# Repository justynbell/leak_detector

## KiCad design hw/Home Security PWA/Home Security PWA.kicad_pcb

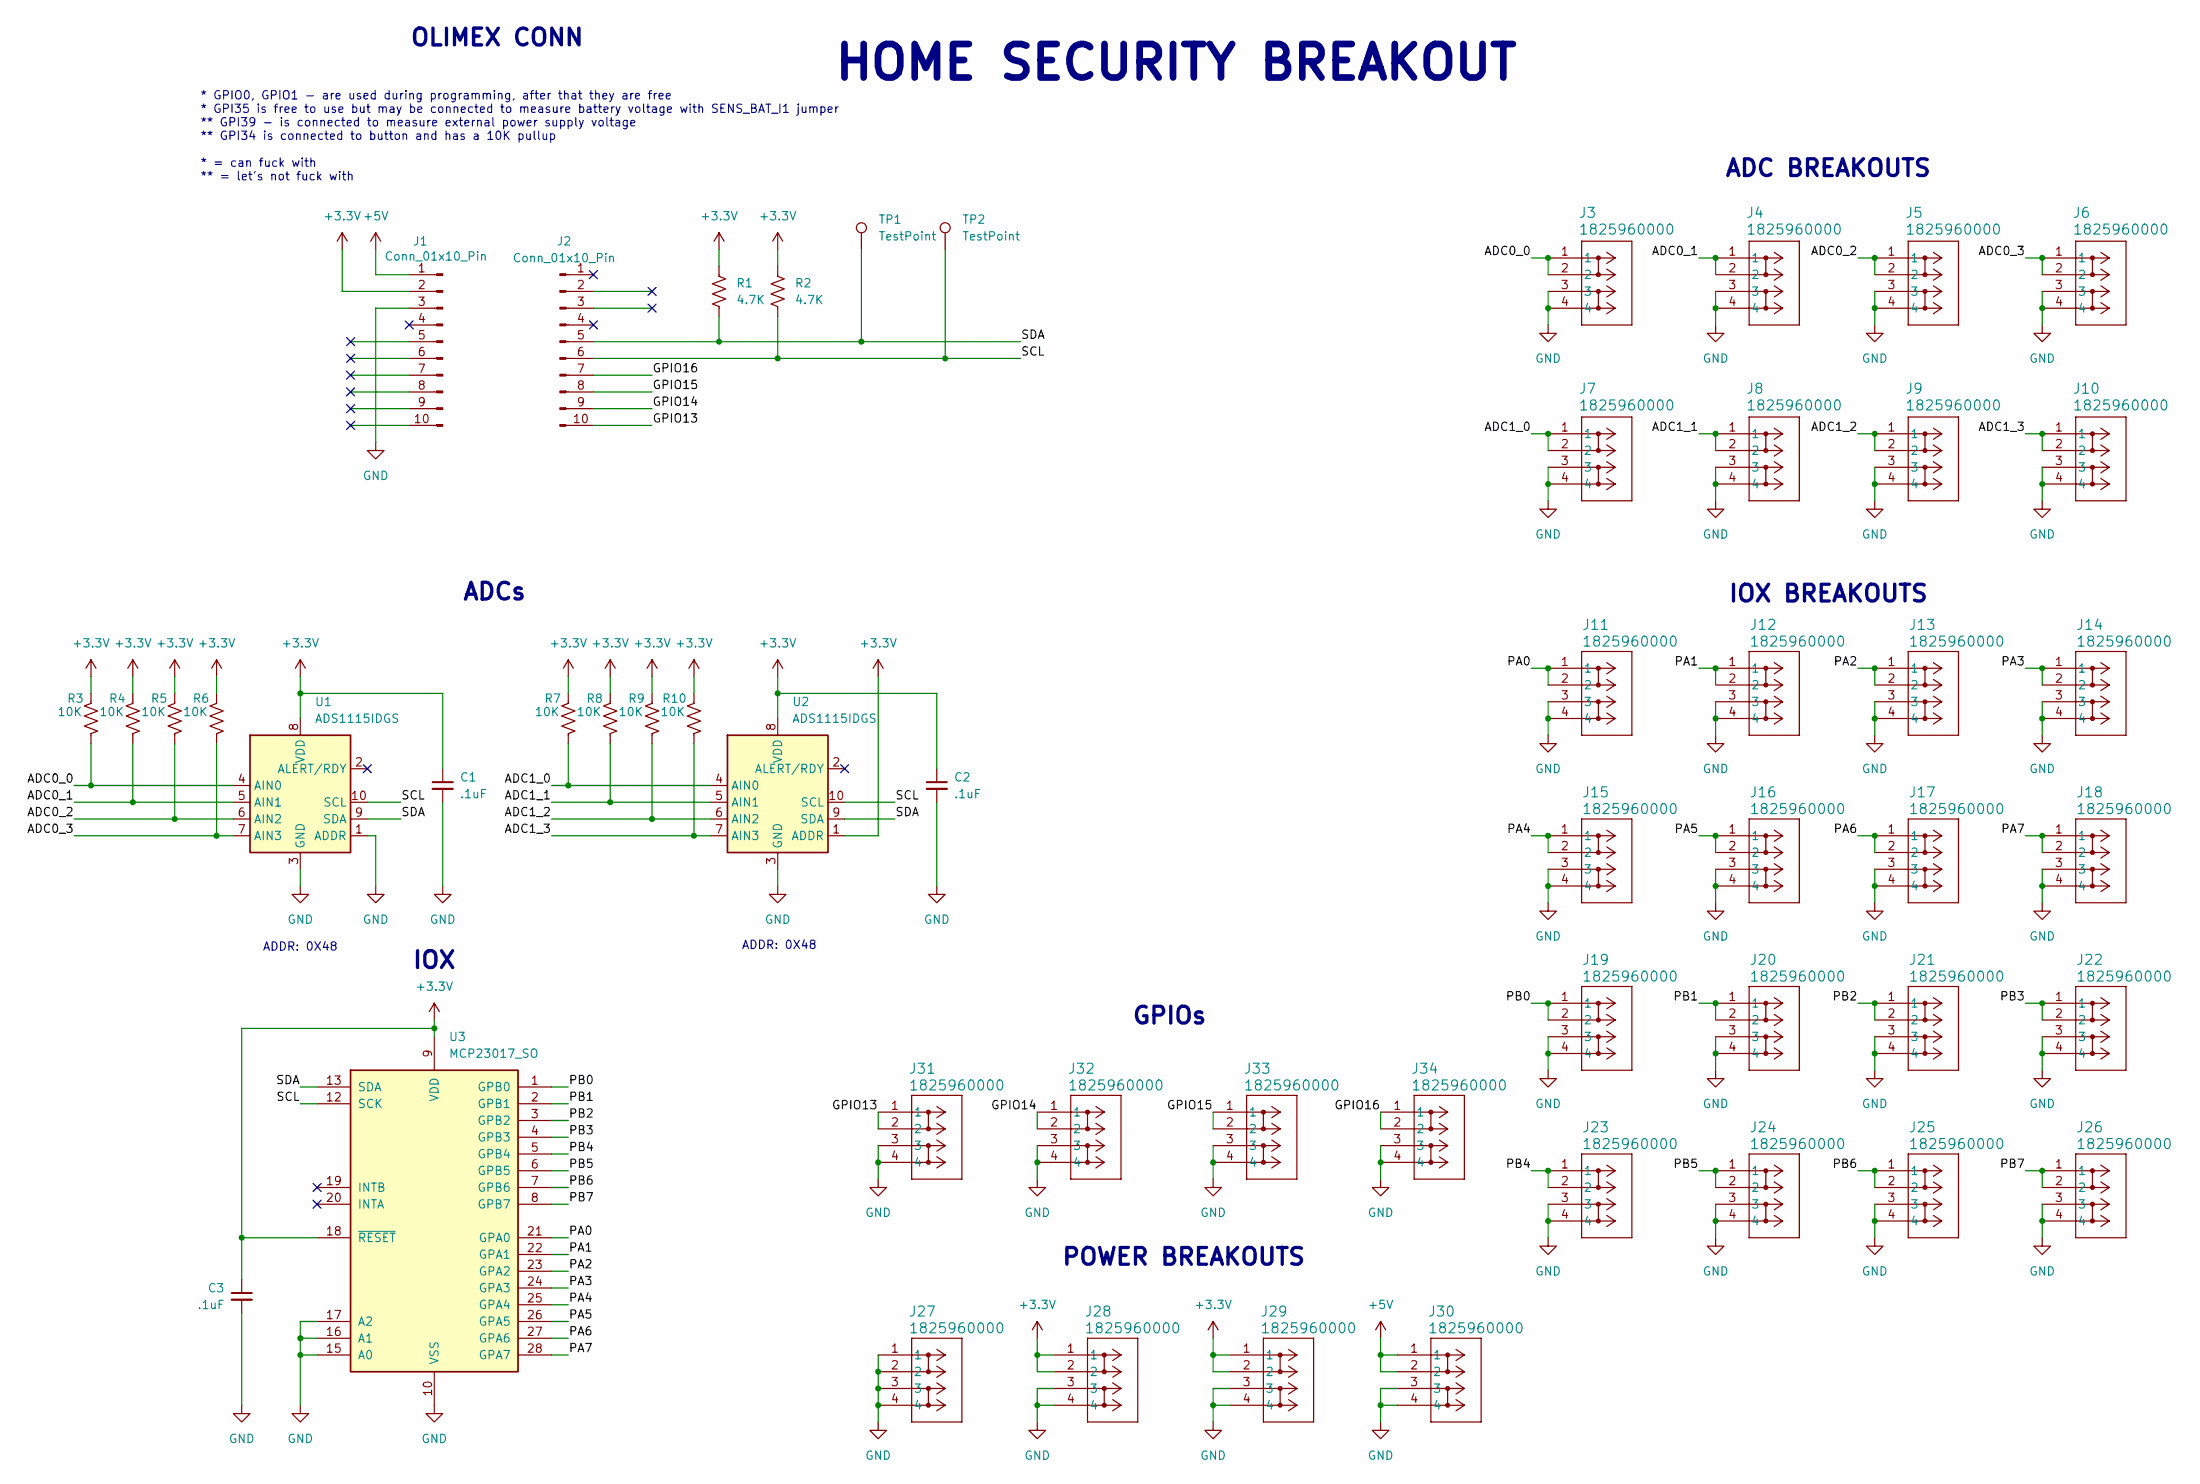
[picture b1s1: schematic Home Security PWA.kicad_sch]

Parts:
C1, C2, C3: .1uF; C_0805_2012Metric_Pad1.18x1.45mm_HandSolder
J1, J2: Conn_01x10_Pin; PPTC101LFBN-RC
J3, J4, J5, J6, J7, J8, J9, J10, J11, J12, J13, J14, J15, J16, J17, J18, J19, J20, J21, J22, J23, J24, J25, J26, J27, J28, J29, J30, J31, J32, J33, J34: 1825960000; CONN_1825960000_WED
R1, R2: 4.7K; R_0805_2012Metric_Pad1.20x1.40mm_HandSolder
R3, R4, R5, R6, R7, R8, R9, R10: 10K; R_0805_2012Metric_Pad1.20x1.40mm_HandSolder
TP1, TP2: TestPoint; TestPoint_THTPad_D2.0mm_Drill1.0mm
U1, U2: ADS1115IDGS; TSSOP-10_3x3mm_P0.5mm
U3: MCP23017_SO; SOIC-28W_7.5x17.9mm_P1.27mm

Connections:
+3.3V: C1.1, C2.1, C3.1, J1.2, J28.1, J28.2, J29.1, J29.2, R1.1, R2.1, R3.1, R4.1, R5.1, R6.1, R7.1, R8.1, R9.1, R10.1, U1.8 (VDD), U2.1 (ADDR), U2.8 (VDD), U3.9 (VDD), U3.18 (~RESET)
+5V: J1.1, J30.1, J30.2
/ADC0_0: J3.1, J3.2, R3.2, U1.4 (AIN0)
/ADC0_1: J4.1, J4.2, R4.2, U1.5 (AIN1)
/ADC0_2: J5.1, J5.2, R5.2, U1.6 (AIN2)
/ADC0_3: J6.1, J6.2, R6.2, U1.7 (AIN3)
/ADC1_0: J7.1, J7.2, R7.2, U2.4 (AIN0)
/ADC1_1: J8.1, J8.2, R8.2, U2.5 (AIN1)
/ADC1_2: J9.1, J9.2, R9.2, U2.6 (AIN2)
/ADC1_3: J10.1, J10.2, R10.2, U2.7 (AIN3)
/GPIO13: J2.10, J31.1, J31.2
/GPIO14: J2.9, J32.1, J32.2
/GPIO15: J2.8, J33.1, J33.2
/GPIO16: J2.7, J34.1, J34.2
/PA0: J11.1, J11.2, U3.21 (GPA0)
/PA1: J12.1, J12.2, U3.22 (GPA1)
/PA2: J13.1, J13.2, U3.23 (GPA2)
/PA3: J14.1, J14.2, U3.24 (GPA3)
/PA4: J15.1, J15.2, U3.25 (GPA4)
/PA5: J16.1, J16.2, U3.26 (GPA5)
/PA6: J17.1, J17.2, U3.27 (GPA6)
/PA7: J18.1, J18.2, U3.28 (GPA7)
/PB0: J19.1, J19.2, U3.1 (GPB0)
/PB1: J20.1, J20.2, U3.2 (GPB1)
/PB2: J21.1, J21.2, U3.3 (GPB2)
/PB3: J22.1, J22.2, U3.4 (GPB3)
/PB4: J23.1, J23.2, U3.5 (GPB4)
/PB5: J24.1, J24.2, U3.6 (GPB5)
/PB6: J25.1, J25.2, U3.7 (GPB6)
/PB7: J26.1, J26.2, U3.8 (GPB7)
/SCL: J2.6, R2.2, TP2.1, U1.10 (SCL), U2.10 (SCL), U3.12 (SCK); also elsewhere on the board
/SDA: J2.5, R1.2, TP1.1, U1.9 (SDA), U2.9 (SDA), U3.13 (SDA); also elsewhere on the board
GND: C1.2, C2.2, C3.2, J1.3, J3.3, J3.4, J4.3, J4.4, J5.3, J5.4, J6.3, J6.4, J7.3, J7.4, J8.3, J8.4, J9.3, J9.4, J10.3, J10.4, J11.3, J11.4, J12.3, J12.4, J13.3, J13.4, J14.3, J14.4, J15.3, J15.4, J16.3, J16.4, J17.3, J17.4, J18.3, J18.4, J19.3, J19.4, J20.3, J20.4, J21.3, J21.4, J22.3, J22.4, J23.3, J23.4, J24.3, J24.4, J25.3, J25.4, J26.3, J26.4, J27.1, J27.2, J27.3, J27.4, J28.3, J28.4, J29.3, J29.4, J30.3, J30.4, J31.3, J31.4, J32.3, J32.4, J33.3, J33.4, J34.3, J34.4, U1.1 (ADDR), U1.3 (GND), U2.3 (GND), U3.10 (VSS), U3.15 (A0), U3.16 (A1), U3.17 (A2)

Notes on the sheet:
GPIOs
HOME SECURITY BREAKOUT
ADC BREAKOUTS
IOX
ADDR: 0X48
IOX BREAKOUTS
OLIMEX CONN
POWER BREAKOUTS
ADCs
* GPIO0, GPIO1 - are used during programming, after that they are free * GPI35 is free to use but may be connected to measure battery voltage with SENS_BAT_I1 jumper ** GPI39 - is connected to measure external power supply voltage ** GPI34 is connected to button and has a 10K pullup * = can fuck wi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

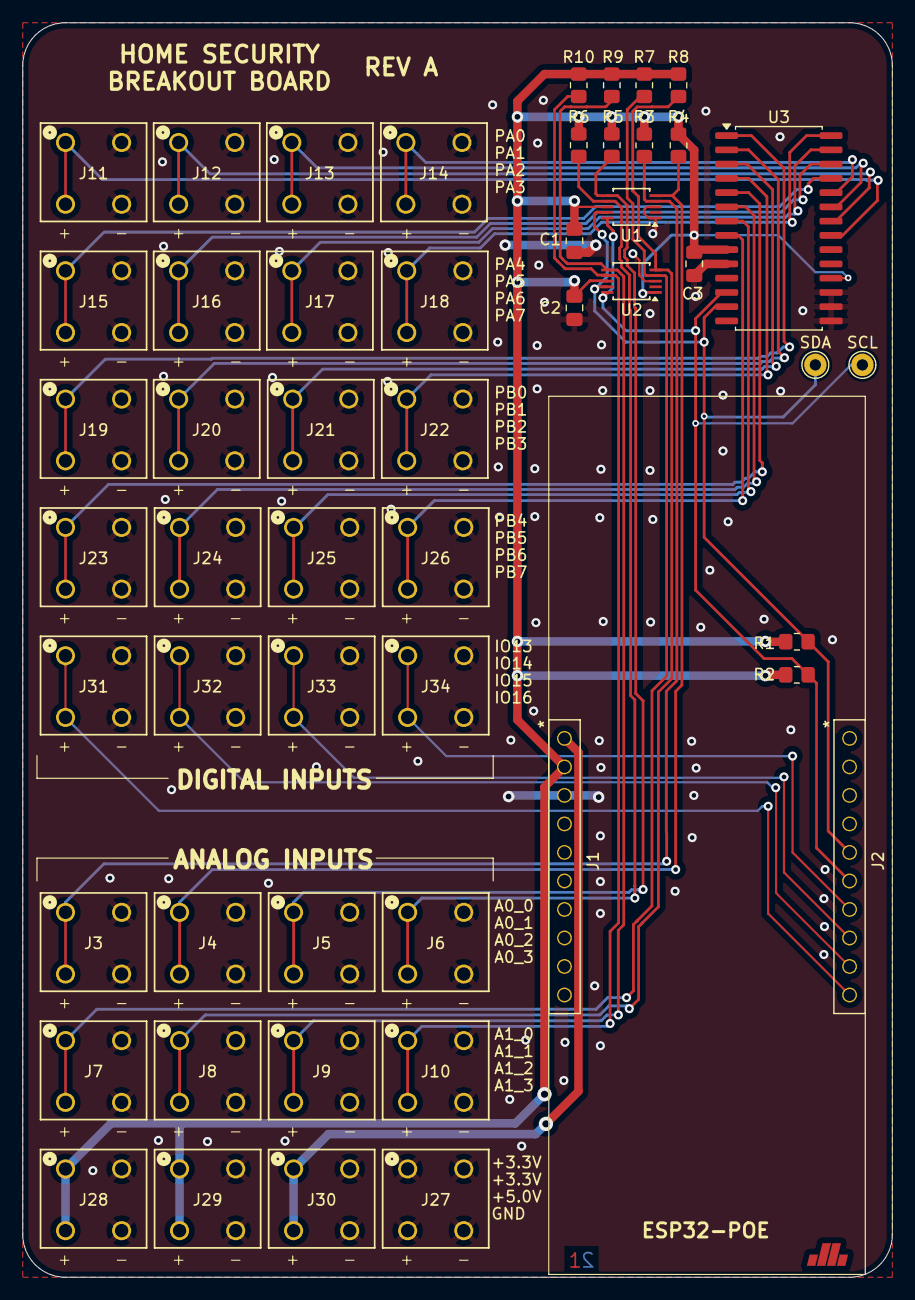
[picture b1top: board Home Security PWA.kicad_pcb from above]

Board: 2 copper layers, 77.5 x 111.8 mm, 52 parts (0 on the bottom side), 33 nets.

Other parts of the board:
SCL: TestPoint; TestPoint_THTPad_D2.0mm_Drill1.0mm
SDA: TestPoint; TestPoint_THTPad_D2.0mm_Drill1.0mm

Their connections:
/SCL: SCL.1; also elsewhere on the board
/SDA: SDA.1; also elsewhere on the board

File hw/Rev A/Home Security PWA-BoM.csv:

"Reference","Qty","Value","DNP","Exclude from BOM","Exclude from Board","Footprint","Datasheet"
"C1,C2,C3","3",".1uF","","","","Capacitor_SMD:C_0805_2012Metric_Pad1.18x1.45mm_HandSolder","~"
"J1,J2","2","Conn_01x10_Pin","","","","footprint:PPTC101LFBN-RC","~"
"J3,J4,J5,J6,J7,J8,J9,J10,J11,J12,J13,J14,J15,J16,J17,J18,J19,J20,J21,J22,J23,J24,J25,J26,J27,J28,J29,J30,J31,J32,J33,J34","32","1825960000","","","","footprint:CONN_1825960000_WED","1825960000"
"R1,R2","2","4.7K","","","","Resistor_SMD:R_0805_2012Metric_Pad1.20x1.40mm_HandSolder","~"
"R3,R4,R5,R6,R7,R8,R9,R10","8","10K","","","","Resistor_SMD:R_0805_2012Metric_Pad1.20x1.40mm_HandSolder","~"
"TP1,TP2","2","TestPoint","","","","TestPoint:TestPoint_THTPad_D2.0mm_Drill1.0mm","~"
"U1,U2","2","ADS1115IDGS","","","","Package_SO:TSSOP-10_3x3mm_P0.5mm","http://www.ti.com/lit/ds/symlink/ads1113.pdf"
"U3","1","MCP23017_SO","","","","Package_SO:SOIC-28W_7.5x17.9mm_P1.27mm","https://ww1.microchip.com/downloads/aemDocuments/documents/A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"

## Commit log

2026-02-04 First cut at leak detector hardware
2026-02-07 Second iteration of leak detector HW.
    Added docs.
2026-02-08 Adding hw/ and sw/
    SW is first (complete) cut.
    HW is a work in progress.
2026-02-08 Update components.
2026-02-08 typo
2026-02-08 Design and layout done.
2026-02-08 Restructuring hw directory.
2026-02-09 Rev A.
    Added these "top" loader cable holders.
    Added GPIOs that directly attach to the ESP32.
2026-02-09 Updates.
